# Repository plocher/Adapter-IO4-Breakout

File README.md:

# Adapter-IO4-Breakout
## License: CERN Open Hardware Licence v1.2

RJ12/6 breakout board, inline IO4-IO4 probe

For circuit debugging and signal integrity verification

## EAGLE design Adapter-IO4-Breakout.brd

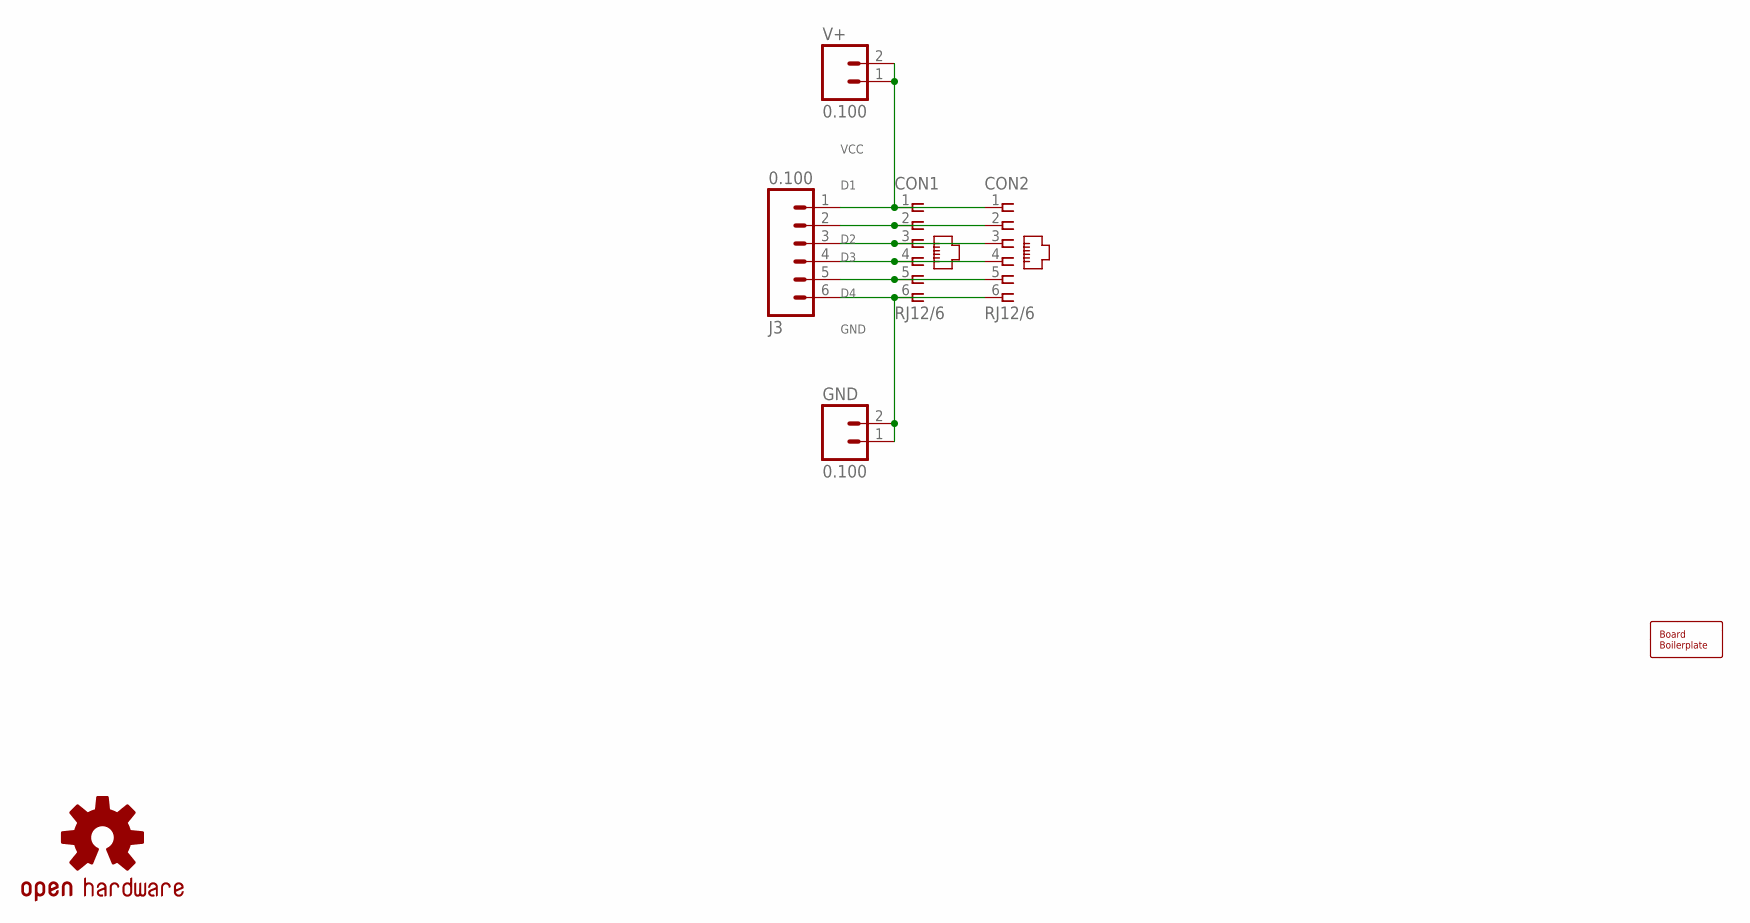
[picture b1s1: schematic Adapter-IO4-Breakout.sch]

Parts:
BOARD1: BOARD; BOARD-SEEED5X5-NOHOLES
CON1, CON2: RJ12/6; RJ25-PANEL
GND: 0.100; 1X02_LOCK
J3: 0.100; 1X06_LOCK
U$1: OSHW; OSHW-LOGO-M
V+: 0.100; 1X02_LOCK

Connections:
D1: CON1.2, CON2.2, J3.2
D2: CON1.3, CON2.3, J3.3
D3: CON1.4, CON2.4, J3.4
D4: CON1.5, CON2.5, J3.5
GND: CON1.6, CON2.6, GND.1 (A), GND.2 (B), J3.6
VCC: CON1.1, CON2.1, J3.1, V+.1 (A), V+.2 (B)

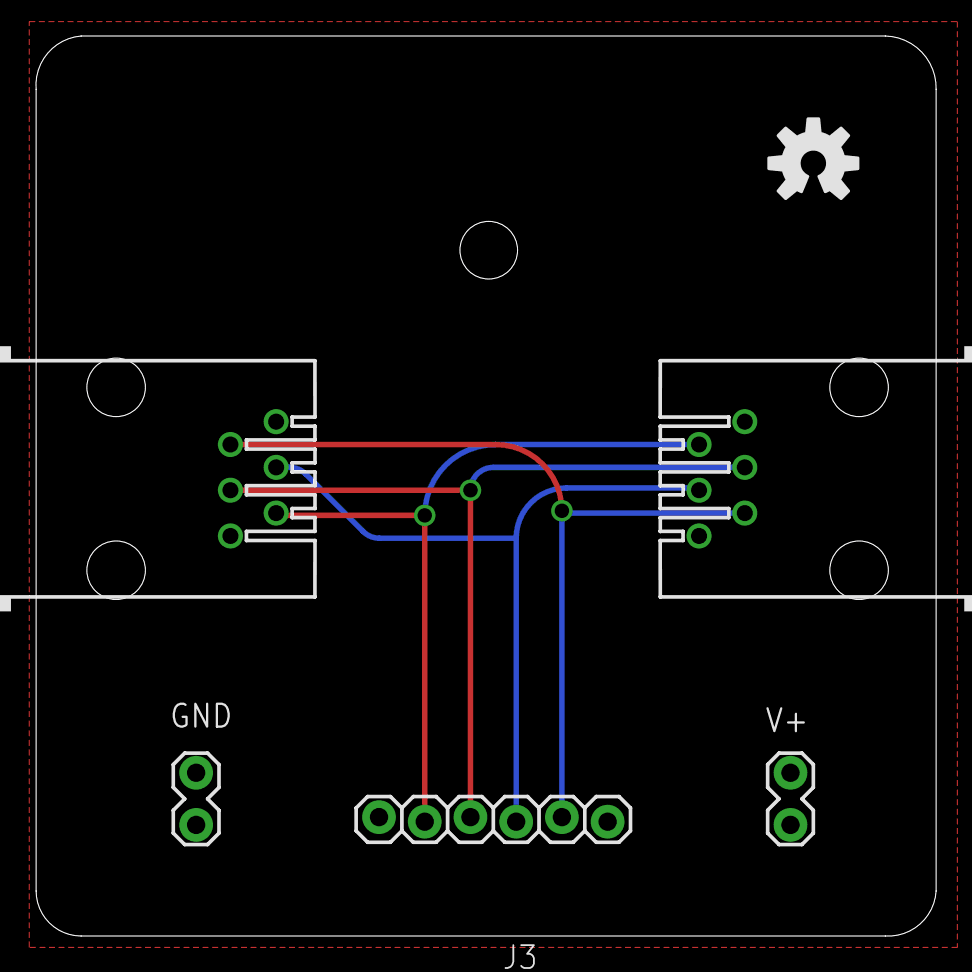
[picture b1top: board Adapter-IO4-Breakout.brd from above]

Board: 2 copper layers, 50.0 x 50.0 mm, 7 parts (0 on the bottom side), 6 nets.

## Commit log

2019-12-09 added graphic
2020-05-04 updated tags
2020-10-05 added values for connectors
2020-10-06 normalized values
